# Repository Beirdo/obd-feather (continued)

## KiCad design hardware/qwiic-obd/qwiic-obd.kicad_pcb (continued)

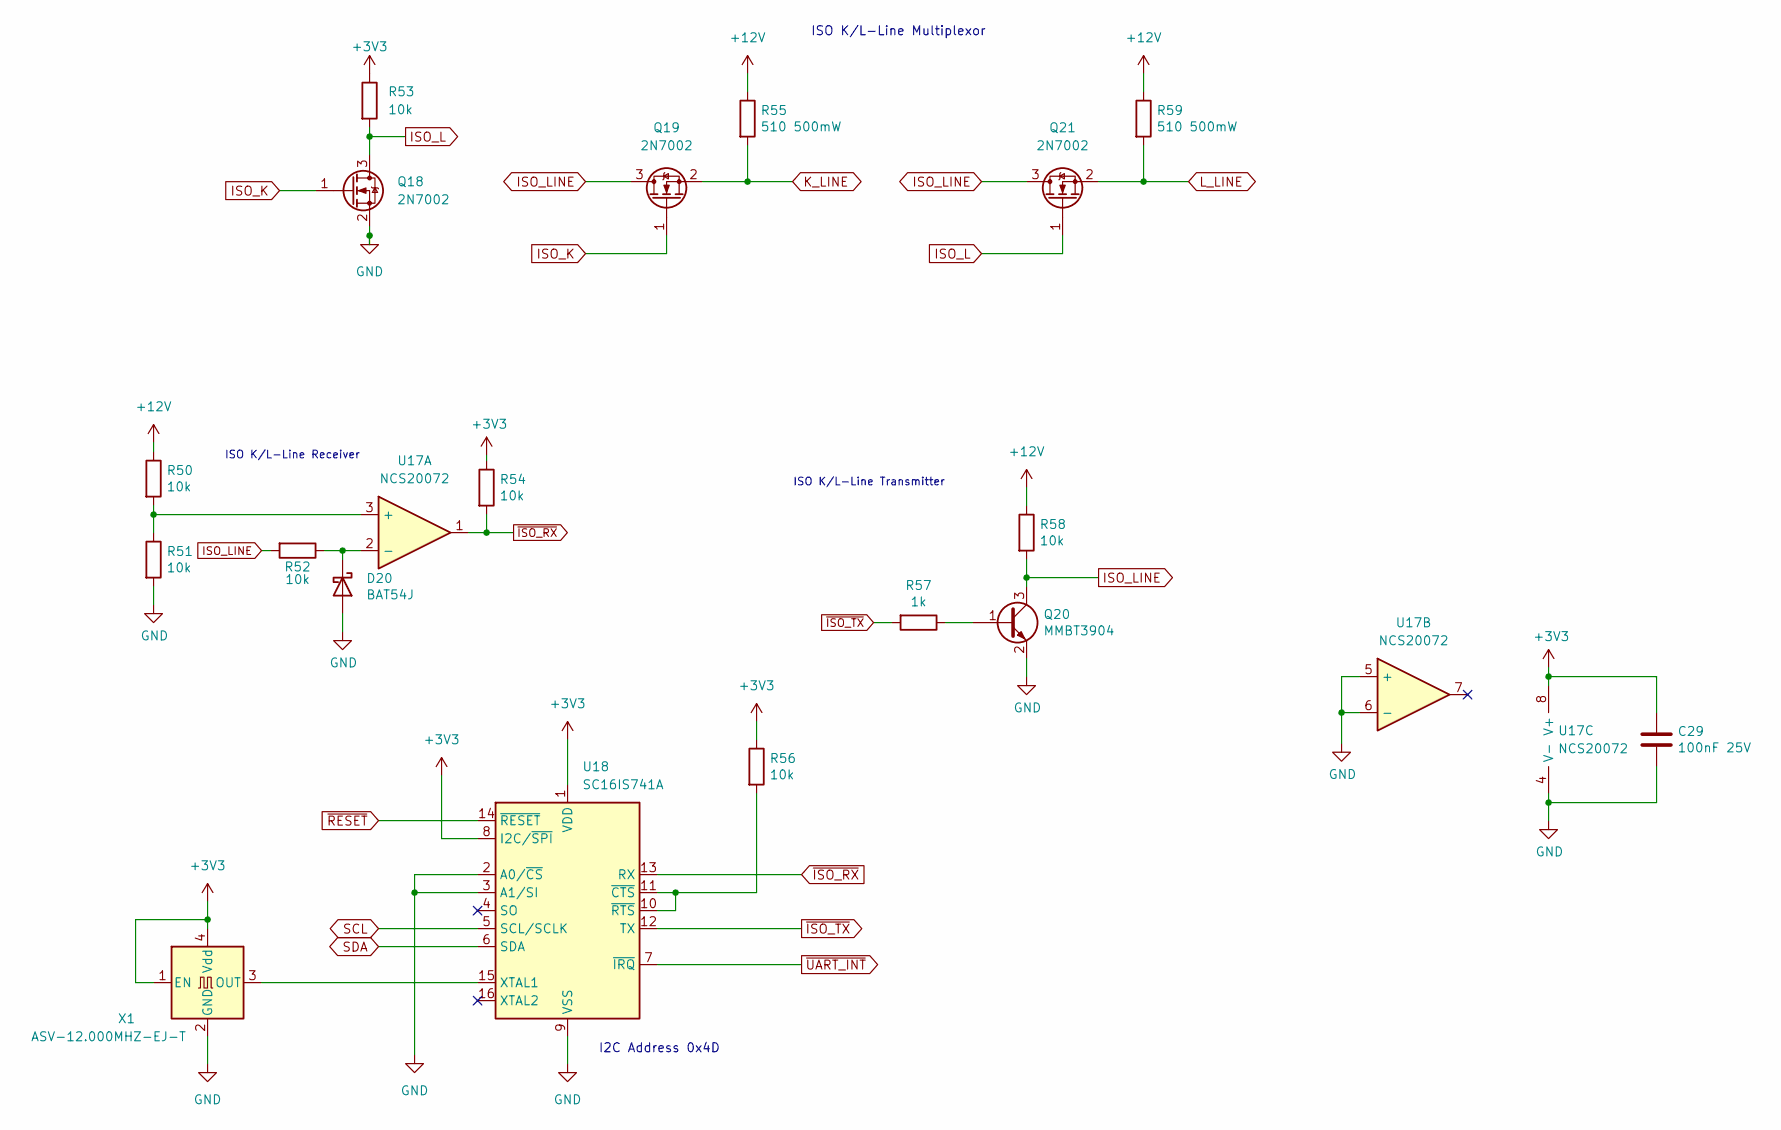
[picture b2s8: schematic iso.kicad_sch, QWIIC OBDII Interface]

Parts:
C29: 100nF 25V; C_0805_2012Metric_Pad1.18x1.45mm_HandSolder
D20: BAT54J; D_SOD-123
Q18, Q19, Q21: 2N7002; SOT-23
Q20: MMBT3904; SOT-23
R50, R51, R52, R53, R54, R56, R58: 10k; R_0805_2012Metric_Pad1.20x1.40mm_HandSolder
R55, R59: 510 500mW; R_1210_3225Metric_Pad1.30x2.65mm_HandSolder
R57: 1k; R_0805_2012Metric_Pad1.20x1.40mm_HandSolder
U17: NCS20072; TSSOP-8_4.4x3mm_P0.65mm
U18: SC16IS741A; TSSOP-16_4.4x5mm_P0.65mm
X1: ASV-12.000MHZ-EJ-T; Oscillator_SMD_Abracon_ASV-4Pin_7.0x5.1mm; Digikey 535-9309-1-ND

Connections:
+3V3: C29.2, R53.1, R54.1, R56.1, U17.8 (V+), U18.1 (VDD), U18.8 (I2C/~SPI), X1.1 (EN), X1.4 (Vdd); also elsewhere on the board
+12V: R50.1, R55.1, R58.1, R59.1; also elsewhere on the board
GND: C29.1, D20.2 (A), Q18.2 (S), Q20.2 (E), R51.2, U17.4 (V-), U17.5 (+), U17.6 (-), U18.2 (A0/~CS), U18.3 (A1/SI), U18.9 (VSS), X1.2 (GND); also elsewhere on the board
ISO_K: Q18.1 (G), Q19.1 (G); also elsewhere on the board
ISO_L: Q18.3 (D), Q21.1 (G), R53.2
ISO_LINE: Q19.3 (D), Q20.3 (C), Q21.3 (D), R52.2, R58.2
K_LINE: Q19.2 (S), R55.2; also elsewhere on the board
L_LINE: Q21.2 (S), R59.2; also elsewhere on the board
unnamed: D20.1 (K), R52.1, U17.2 (-)
unnamed: Q20.1 (B), R57.1
unnamed: R50.2, R51.1, U17.3 (+)
unnamed: R56.2, U18.10 (~RTS), U18.11 (~CTS)
unnamed: U18.15 (XTAL1), X1.3 (OUT)
SCL: U18.5 (SCL/SCLK); also elsewhere on the board
SDA: U18.6 (SDA); also elsewhere on the board
~ISO_RX: R54.2, U17.1, U18.13 (RX)
~ISO_TX: R57.2, U18.12 (TX)
~RESET: U18.14 (~RESET); also elsewhere on the board
~UART_INT: U18.7 (~IRQ); also elsewhere on the board

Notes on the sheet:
I2C Address 0x4D
ISO K/L-Line Transmitter
ISO K/L-Line Receiver
ISO K/L-Line Multiplexor

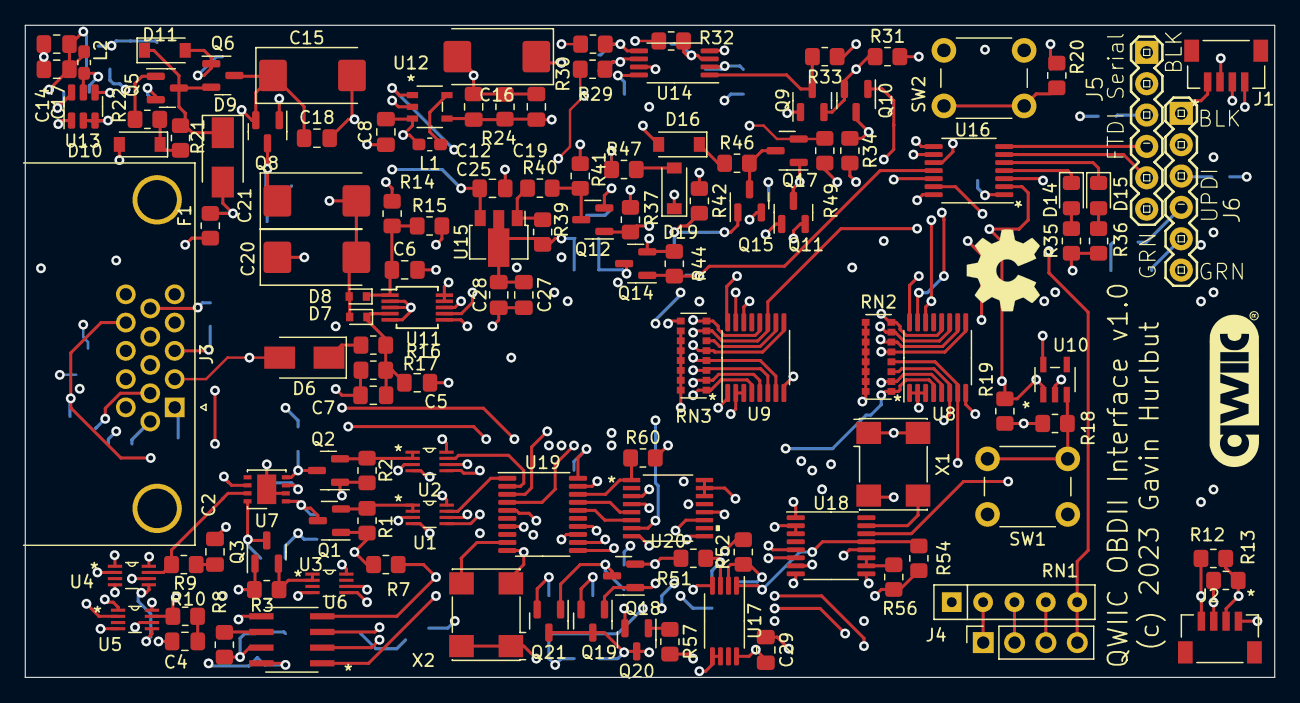
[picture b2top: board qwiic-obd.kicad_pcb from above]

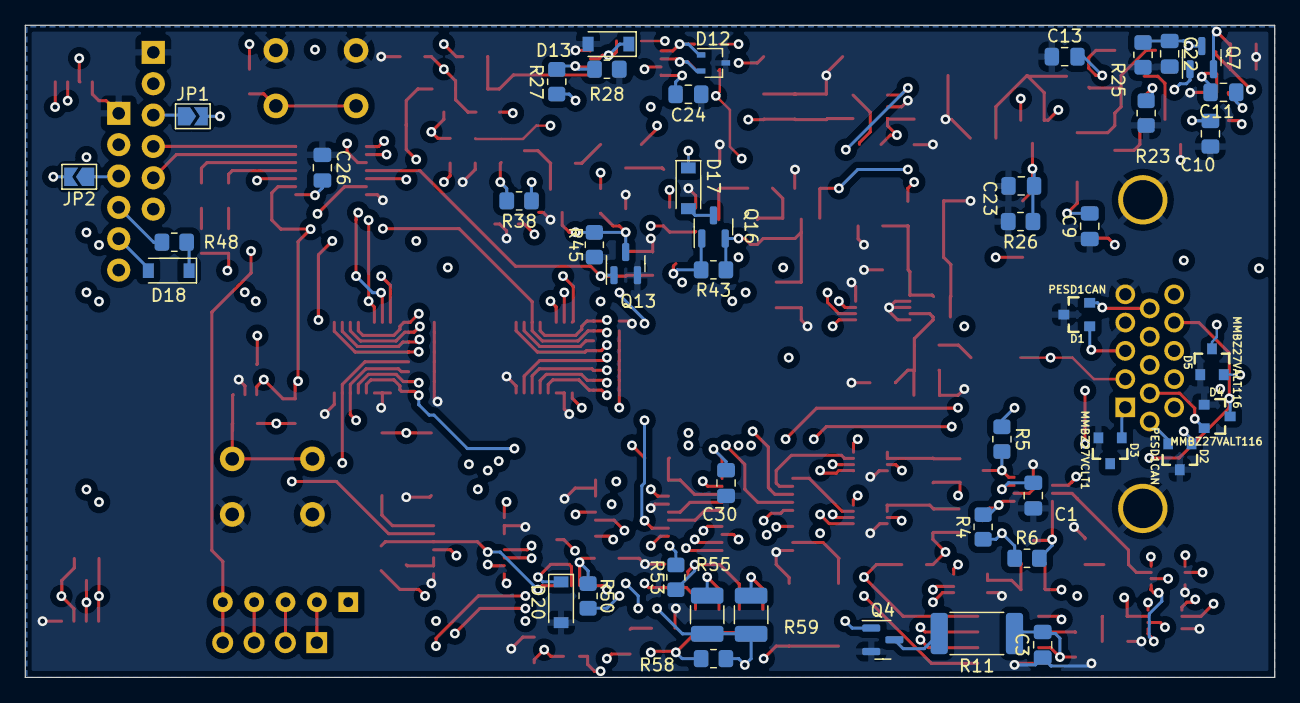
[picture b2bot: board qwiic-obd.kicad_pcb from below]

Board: 4 copper layers, 101.2 x 52.8 mm, 169 parts (45 on the bottom side), 111 nets.

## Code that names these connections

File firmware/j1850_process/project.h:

#ifndef __project_h_
#define __project_h_

#include <Arduino.h>
#include <CircularBuffer.h>

#define PIN_UPDI	      PIN_PA0
#define PIN_J1850_TX    PIN_PA1
#define PIN_J1850_RX    PIN_PA2
#define PIN_J1850_INT   PIN_PA3
#define PIN_RESET       PIN_PA4
#define PIN_SAE_PWM     PIN_PA5
#define PIN_AVR_LED     PIN_PA6
#define PIN_J1850_LED   PIN_PA7
#define PIN_SCL         PIN_PB0
#define PIN_SDA         PIN_PB1
#define PIN_AVR_TX      PIN_PB2
#define PIN_AVR_RX      PIN_PB3

#define I2C_SLAVE_ADDR  0x79

#define MAX_PACKET_SIZE 12          // defined in the SAE J1850 spec
#define CH_SOF          ((uint8_t)0x7E)
#define CH_ESC          ((uint8_t)0x7D)
#define CH_ABORT        ((uint8_t)(CH_SOF ^ 0x80))

#define HI_BYTE(x)     ((uint8_t)(((int)(x) >> 8) & 0xFF))
#define LO_BYTE(x)     ((uint8_t)(((int)(x) & 0xFF)))

#define HI_NIBBLE(x)  ((uint8_t)(((int)(x) >> 4) & 0x0F))
#define LO_NIBBLE(x)  ((uint8_t)(((int)(x) & 0x0F)))

#define BIT(x)        (1 << (x))


extern CircularBuffer<uint8_t, 128> rxRingBuf;
extern CircularBuffer<uint8_t, 128> txRingBuf;
extern int rxPacketCount;

void setOutboundInterrupt(void);


template <typename T>
inline T clamp(T value, T minval, T maxval)
{
  return max(min(value, maxval), minval);
}

template <typename T>
inline T map(T x, T in_min, T in_max, T out_min, T out_max)
{
  // the perfect map fonction, with constraining and float handling
  x = clamp<T>(x, in_min, in_max);
  return (x - in_min) * (out_max - out_min) / (in_max - in_min) + out_min;
}


#endif

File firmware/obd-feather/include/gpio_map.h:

#ifndef __GPIO_MAP_H_
#define __GPIO_MAP_H_

#ifdef __cplusplus
extern "C" {
#endif

#include <device.h>
#include <drivers/gpio.h>

extern struct gpio_dt_spec gpio_input_specs[];
extern const int gpio_input_count;

extern struct gpio_dt_spec gpio_output_specs[];
extern const int gpio_output_count;

typedef enum {
    GPIO_J1850_RX = 0,
} gpio_input_t;

typedef enum {
    GPIO_J1850_TX = 0,
    GPIO_SAE_PWM,
    GPIO_CAN_EN,
    GPIO_CAN_SEL0,
    GPIO_CAN_SEL1,
    GPIO_SW_CAN_MODE0,
    GPIO_SW_CAN_MODE1,
    GPIO_SW_CAN_LOAD,
    GPIO_KLINE_EN,
    GPIO_ISO_K,
    GPIO_NEOPIXEL,
} gpio_output_t;

void gpio_init(void);
void gpio_output_set(int index, bool value);
bool gpio_input_get(int index);
void gpio_irq_enable(int index);
void gpio_irq_disable(int index);


#ifdef __cplusplus
}
#endif

#endif

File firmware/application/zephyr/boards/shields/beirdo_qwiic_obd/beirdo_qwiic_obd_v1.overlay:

#include <dt-bindings/adc/adc.h>
#include "feather_connector.dtsi"

&feather_i2c {
	/* 0x28 */
	spi_bridge_shield: spi_bridge@50 {
		compatible = "nxp,sc18is602b";
		status = "okay";
		spi-max-frequency = <1843000>;
		reg = <0x50>;
		#address-cells = <1>;
		#size-cells = <0>;
		irq-gpios = <&feather_header 14 GPIO_ACTIVE_LOW>;	/* SPI_INT -> D5 */

		can0_shield: can@0 {
			compatible = "microchip,mcp2515";
			status = "okay";
			spi-max-frequency = <10000000>;
			osc-freq = <12000000>;
			bus-speed = <1000000>;
			reg = <0>;
			irq-gpios = <&feather_header 15 GPIO_ACTIVE_LOW>;  /* CAN_INT -> D6 */
		};
	};

	/* 0x20 */
	gpio0_shield: gpio@40 {
		compatible = "ti,tca9538";
		status = "okay";
		reg = <0x40>;
	};

	/* 0x21 */
	gpio1_shield: gpio@42 {
		compatible = "ti,tca9538";
		status = "okay";
		reg = <0x42>;
	};

	/* 0x68 */
	adc_shield: adc@D0 {
		#address-cells = <1>;
		#size-cells = <0>;
		compatible = "microchip,mcp3423";
		status = "okay";
		reg = <0xD0>;

		channel@0 {
			reg = <0>;
			zephyr,gain = "ADC_GAIN_1";
			zephyr,reference = "ADC_REF_INTERNAL";
			/* 16 bits, 15 SPS. */
			zephyr,acquisition-time = <ADC_ACQ_TIME_DEFAULT>;
			zephyr,resolution = <16>;
			zephyr,vref-mv = <2048>;
		};

		channel@1 {
			reg = <1>;
			zephyr,gain = "ADC_GAIN_1";
			zephyr,reference = "ADC_REF_INTERNAL";
			/* 16 bits, 15 SPS. */
			zephyr,acquisition-time = <ADC_ACQ_TIME_DEFAULT>;
			zephyr,resolution = <16>;
			zephyr,vref-mv = <2048>;
		};
	};

	/* 0x79 */
	can1_shield: j1850@F2 {
		compatible = "beirdo,j1850process";
		status = "okay";
		reg = <0xF2>;
		irq-gpios = <&feather_header 16 GPIO_ACTIVE_LOW>;	/* J1850_INT -> D9 */
	};

	/* 0x4D */
	uart0_shield: uart@9A {
		compatible = "nxp,sc16is741a";
		status = "okay";
		current-speed = <10400>;
		reg = <0xF2>;
		irq-gpios = <&feather_header 17 GPIO_ACTIVE_LOW>;	/* UART_INT -> D10 */
	};
};

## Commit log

2023-01-03 Get it all connected (had a few unrouted glitches)
2023-01-03 OK, layout v1 complete
2023-01-03 More silkscreen fun
2023-01-03 Initial content commit
2023-01-03 Added initial layout (parts dump)
2023-01-03 And broke the ground plane again... fixed.
2023-01-03 First revision of PIC firmware source (not tested)
2023-01-03 Firmware now compiles. simulation later.
2023-01-03 Fix a few tweaks
2023-01-03 Like I remember
2023-01-03 Fix title block
2023-01-03 Fix a couple dumb bugs
2023-01-04 Add PIC bootloader, update silkscreen
2023-01-04 Added MCC bootloader with minor tweaks
2023-01-04 Split firmware into two separate projects
    - got it building into different parts of the FLASH.
    - bootloader - 0x000 - 0x3FF (word addresses)
    - application - 0x400 - end (word addresses)
    - reset vector and interrupt vector are also mirrored
    into 0x400 and 0x404 (respectively) for application
    use, and are linked to from the bootloader
2023-01-05 Added BL_LED on PA0, with a jumper
    - if using ICSP, move jumper to 2,3 and PA0 is ISCPDAT
    - if using bootloader, move jumper to 1,2 and PA0 is the LED
2023-01-05 Turn on boot block write protect
    - I'm a bit concerned that both the boot loader and the app are pushing
    the config values, and that this might break in a fun way.
2023-01-05 Added gerbers
2023-01-06 Changed DB15HD connector, fixed layout
2023-01-09 Shrunk layout a bit
2023-01-10 Adding initial shield definition
2023-01-10 Fill out shield definition
    - here's hoping I did this right. Until I have application code to
    compile (and drivers), I won't know.
2023-01-10 First run at a driver for the MCP342x ADC series
2023-01-10 Add first run at SC18IS602B driver, add some data sheets
2023-01-10 Added SC16IS741A UART and added datasheet
2023-01-27 Make timings table driven
    - not sure that I finished this
2023-01-27 Moved to using shared KiCad libs, regen gerbers
2023-02-07 Add a readme for the PIC firmware
2023-02-08 Switch out the PIC for an ATtiny424.
2023-02-08 Time to redo the firmware in Arduino
2023-02-08 Start porting the firmware over
    - still need to do the actual IO.
2023-02-08 J1850 TX is coded. RX will wait until X hours of sleep
2023-02-08 Looks like we need direct port access
    - pulseIn needs the pulse to be isolated (LOW-HIGH-LOW)
    - we need to find the next edge... so interrupt handler on both edges.
2023-02-08 There's the VPW receive code. This is gonna be fun to test!
2023-02-08 Remove the old PIC firmware
2023-02-08 Added Queue to the library list
2023-02-08 Only delay if there's a positive delay.
2023-02-17 Update firmware README
2023-02-25 Moved git libs to new repo
    - https://github.com/Beirdo/KiCad-Git-Libraries
2023-03-09 Moved j1850_process to PlatformIO
2023-03-10 Started moving the qwiic-obd firmware over to PlatformIO
    - targeting the Adafruit F405 Express Feather board, running zephyr
2023-03-13 Redid the entire design to be a large feather-wing
2023-03-13 Update schematic PDF
2023-03-13 Forgot to save...
2023-03-13 Renamed the shield, removed cruft.
    - may want to add the GPIO definitions (?)
2023-03-13 Remove unused cruft.
2023-03-13 Rename the board in PlatformIO
2023-03-13 rename application -> obd-feather
2023-03-13 Add in the sample CAN application as a starting place
2023-03-13 Adding more drivers, labelling the external GPIO
2023-03-13 Seems I might need to write a driver for TCA9534
    - or extend the PCA953x, which currently supports only TCA9538
2023-03-13 Got it compiling with SSD1306 support, and ADC enabled
2023-03-14 Add in display and CAN code startings.
2023-03-14 Add in GPIO nodes in preparation for adding them in code
2023-03-14 Added GPIO map
2023-03-14 Add support for mode switching and scanning
    - scanning incomplete as it will just assume that it's getting traffic
    as there is no mechanism in yet to indicate traffic flow
2023-03-14 Start the C++ implementation
    - still stuck on how I want to do the receive path for the moment
2023-03-14 Ooops, PID number is actually only one byte
    - need to refactor into an OBDII buffer
2023-03-20 Added in KLine support (ISO9141 and ISO-14230/KWP)
2023-03-21 Add J1850 code, deleted old TinyAVR code
2023-03-21 Added better abort support for J1850
2023-03-21 Moved GPIO control into the port classes
2023-03-21 Add support to mount an SD card at /SD
    - will need to deal with the eventuality of no card detected.
